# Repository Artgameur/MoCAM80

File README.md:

<p align="center">

</p>

# Table of Contents

* [Introduction](#Introduction)
* [Quick Description](#Quick-Description)
* [Firmware](#Firmware)
* [Architecture](#Architecture)
* [Features](#Features)
* [Images](#Images)
* [Components](#Components)
* [Instructions](#Instructions)
* [Schematic](#Schematic)
* [PCB](#PCB)

# Introduction

This is a project that I made for fun and to challenge myself during my second year of college as an electrical engineering student. Since I was working at 3dkeycap (a small-scale customizable keycap manufacturer), I thought about making a mechanical split keyboard. Since I was using a standard-size optical keyboard and my father is a programmer, I thought of making one for him too. This also happens to be my first GitHub repository.

Since I didn't know much about split keyboards, the thumb cluster ended up being a little unusual. Because I was making a keyboard for a programmer, it had to have a function row. At that point, I knew that the keyboard was going to be larger than standard layouts such as the Lily58 or Corne. Since it was already going to be that large, I thought, "Why not make it bigger?" So I ended up adding 80 keys.

So here is my finished project.

# Quick Description

MoCAM80 is a raspberry pi pico 2 powered 80 key split machanical keyboard. It has a reversible PCB design so that there is only one PCB version for both sides.

# Firmware

The keyboard uses custom firmware written specifically for the MoCAM80.

The left half acts as the primary controller while the right half operates as a secondary controller connected through TRRS via UART. Precompiled UF2 files are provided in the repository for both halves.

# Architecture

* Left PCB: main controller (USB HID)
* Right PCB: secondary matrix scanner
* Communication: UART via TRRS
* Firmware: custom C/C++

# Features

* A 6-key thumb cluster
* A number row
* A function row
* A 3D-printable case
* A reversible PCB (the same design is used for both sides)

# Images

# Components

## PCB Assembly

### Required
| Quantity | Component |
|----------|-----------|
| 80 | Choc V2 switches |
| 80 | MX low-profile keycaps |
| 2 | Raspberry Pi Pico 2 |
| 2 | TRRS (4-pole) female connectors |
| 1 | TRRS (4-pole) cable |
| 1 | Micro-USB data cable |

### Optional
| Quantity | Component |
|----------|-----------|
| 12 | 10 kΩ resistors (internal pull-ups are enabled) |

## Case
| Material | Quantity |
|----------|-----------|
| filament | 300g |

# Instructions

1. Once you have 2 PCBs, solder 1 Raspberry Pi Pico 2 onto each PCB.

2. Solder 1 female TRRS connector onto each PCB. (Be careful when handling them, as excessive force while plugging or unplugging the cable may lift pads from the PCB.)

3. Solder 40 switches onto one PCB and 40 switches onto the other PCB.

4. OPTIONAL: Solder 6 10 kΩ resistors onto each PCB.

5. On the left-hand PCB (the one with the switches on the same side as the Pico 2 and the TRRS connector), cut the upper two traces shown below, located near the bottom-right corner of the Pico 2.

6. On the right-hand PCB (the one with the switches on the opposite side of the Pico 2 and the TRRS connector), cut the lower two traces shown below, located near the bottom-right corner of the Pico 2.

7. Upload the [UF2 file for the main board](Software/Compiled%20Files/keyboard_Main.uf2) to the left-hand PCB.

8. Upload the [UF2 file for the secondary board](Software/Compiled%20Files/keyboard_Secondary.uf2) to the right-hand PCB.

9. Confirm that everything works correctly.

10. Print the case and assemble the final product.

# Schematic

# PCB
## Top Side

## Bottom Side

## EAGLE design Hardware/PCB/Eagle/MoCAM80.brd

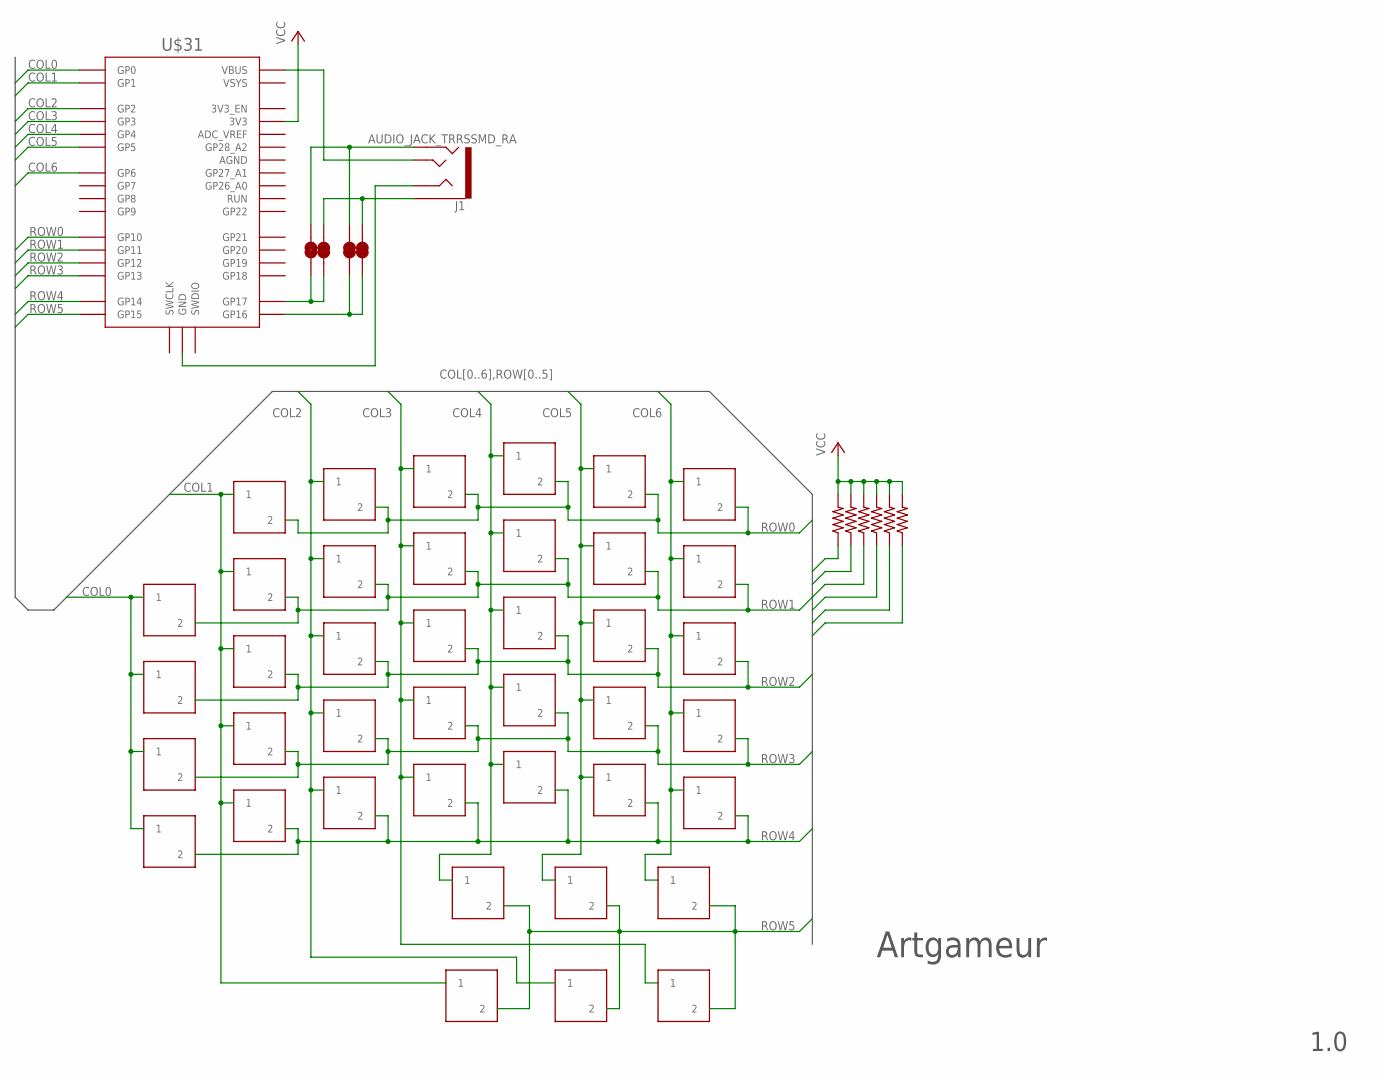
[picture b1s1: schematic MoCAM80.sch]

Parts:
J1: AUDIO_JACK_TRRSSMD_RA; AUDIO_JACK_3.5MM_TRRS_SMD_RA
JP1, JP2, JP3, JP4: JUMPER-SMT_2_NC_TRACE_NO-SILK; SMT-JUMPER_2_NC_TRACE_NO-SILK
R1, R2, R3, R4, R5, R6: R-US_CHIP-1206(3216-METRIC); RESC3216X70
U$1, U$2, U$3, U$4, U$5, U$6, U$7, U$8, U$9, U$10, U$11, U$12, U$13, U$14, U$15, U$16, U$17, U$18, U$19, U$21, U$22, U$23, U$24, U$26, U$27, U$28, U$29, U$32, U$33, U$34, U$35, U$36, U$37, U$38: KEYBOARD_SWITCHMX_CHOC_V2_SWAP; MX_CHOC_V2_SWAP
U$20, U$25: KEYBOARD_SWITCHMX_CHOC_V2_1.25; MX_CHOC_V2_1.25
U$30, U$39, U$40, U$41: KEYBOARD_SWITCHMX_CHOC_V2_1.5; MX_CHOC_V2_1.5
U$31: RPI_PICO-SMD; RPI_PICO

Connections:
COL0: U$1.P$1 (1), U$1.P$4 (1), U$2.P$1 (1), U$2.P$4 (1), U$3.P$1 (1), U$3.P$4 (1), U$31.GP0, U$38.P$1 (1), U$38.P$4 (1)
COL1: U$4.P$1 (1), U$4.P$4 (1), U$5.P$1 (1), U$5.P$4 (1), U$6.P$1 (1), U$6.P$4 (1), U$7.P$1 (1), U$7.P$4 (1), U$20.P$1 (1), U$20.P$4 (1), U$31.GP1, U$32.P$1 (1), U$32.P$4 (1)
COL2: U$8.P$1 (1), U$8.P$4 (1), U$9.P$1 (1), U$9.P$4 (1), U$10.P$1 (1), U$10.P$4 (1), U$11.P$1 (1), U$11.P$4 (1), U$25.P$1 (1), U$25.P$4 (1), U$31.GP2, U$33.P$1 (1), U$33.P$4 (1)
COL3: U$12.P$1 (1), U$12.P$4 (1), U$13.P$1 (1), U$13.P$4 (1), U$14.P$1 (1), U$14.P$4 (1), U$15.P$1 (1), U$15.P$4 (1), U$31.GP3, U$34.P$1 (1), U$34.P$4 (1), U$39.P$1 (1), U$39.P$4 (1)
COL4: U$16.P$1 (1), U$16.P$4 (1), U$17.P$1 (1), U$17.P$4 (1), U$18.P$1 (1), U$18.P$4 (1), U$19.P$1 (1), U$19.P$4 (1), U$30.P$1 (1), U$30.P$4 (1), U$31.GP4, U$35.P$1 (1), U$35.P$4 (1)
COL5: U$21.P$1 (1), U$21.P$4 (1), U$22.P$1 (1), U$22.P$4 (1), U$23.P$1 (1), U$23.P$4 (1), U$24.P$1 (1), U$24.P$4 (1), U$31.GP5, U$36.P$1 (1), U$36.P$4 (1), U$40.P$1 (1), U$40.P$4 (1)
COL6: U$26.P$1 (1), U$26.P$4 (1), U$27.P$1 (1), U$27.P$4 (1), U$28.P$1 (1), U$28.P$4 (1), U$29.P$1 (1), U$29.P$4 (1), U$31.GP6, U$37.P$1 (1), U$37.P$4 (1), U$41.P$1 (1), U$41.P$4 (1)
JACK_1: J1.TIP, U$31.VBUS
JACK_2: J1.RING2, JP2.2, JP4.2
JACK_GND: J1.RING1, U$31.GND@1 (GND), U$31.GND@2 (GND), U$31.GND@3 (GND), U$31.GND@4 (GND), U$31.GND@5 (GND), U$31.GND@6 (GND), U$31.GND@7 (GND), U$31.GND@8 (GND)
JACK_TIP: J1.EARTH, JP1.2, JP3.2
ROW0: R6.1, U$31.GP10, U$32.P$2 (2), U$33.P$2 (2), U$34.P$2 (2), U$35.P$2 (2), U$36.P$2 (2), U$37.P$2 (2)
ROW1: R1.1, U$4.P$2 (2), U$8.P$2 (2), U$12.P$2 (2), U$16.P$2 (2), U$21.P$2 (2), U$26.P$2 (2), U$31.GP11, U$38.P$2 (2)
ROW2: R2.1, U$1.P$2 (2), U$5.P$2 (2), U$9.P$2 (2), U$13.P$2 (2), U$17.P$2 (2), U$22.P$2 (2), U$27.P$2 (2), U$31.GP12
ROW3: R3.1, U$2.P$2 (2), U$6.P$2 (2), U$10.P$2 (2), U$14.P$2 (2), U$18.P$2 (2), U$23.P$2 (2), U$28.P$2 (2), U$31.GP13
ROW4: R4.1, U$3.P$2 (2), U$7.P$2 (2), U$11.P$2 (2), U$15.P$2 (2), U$19.P$2 (2), U$24.P$2 (2), U$29.P$2 (2), U$31.GP14
ROW5: R5.1, U$20.P$2 (2), U$25.P$2 (2), U$30.P$2 (2), U$31.GP15, U$39.P$2 (2), U$40.P$2 (2), U$41.P$2 (2)
UART_RX: JP1.1, JP4.1, U$31.GP17
UART_TX: JP2.1, JP3.1, U$31.GP16
VCC: R1.2, R2.2, R3.2, R4.2, R5.2, R6.2, U$31.3V3

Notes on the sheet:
Artgameur
1.0

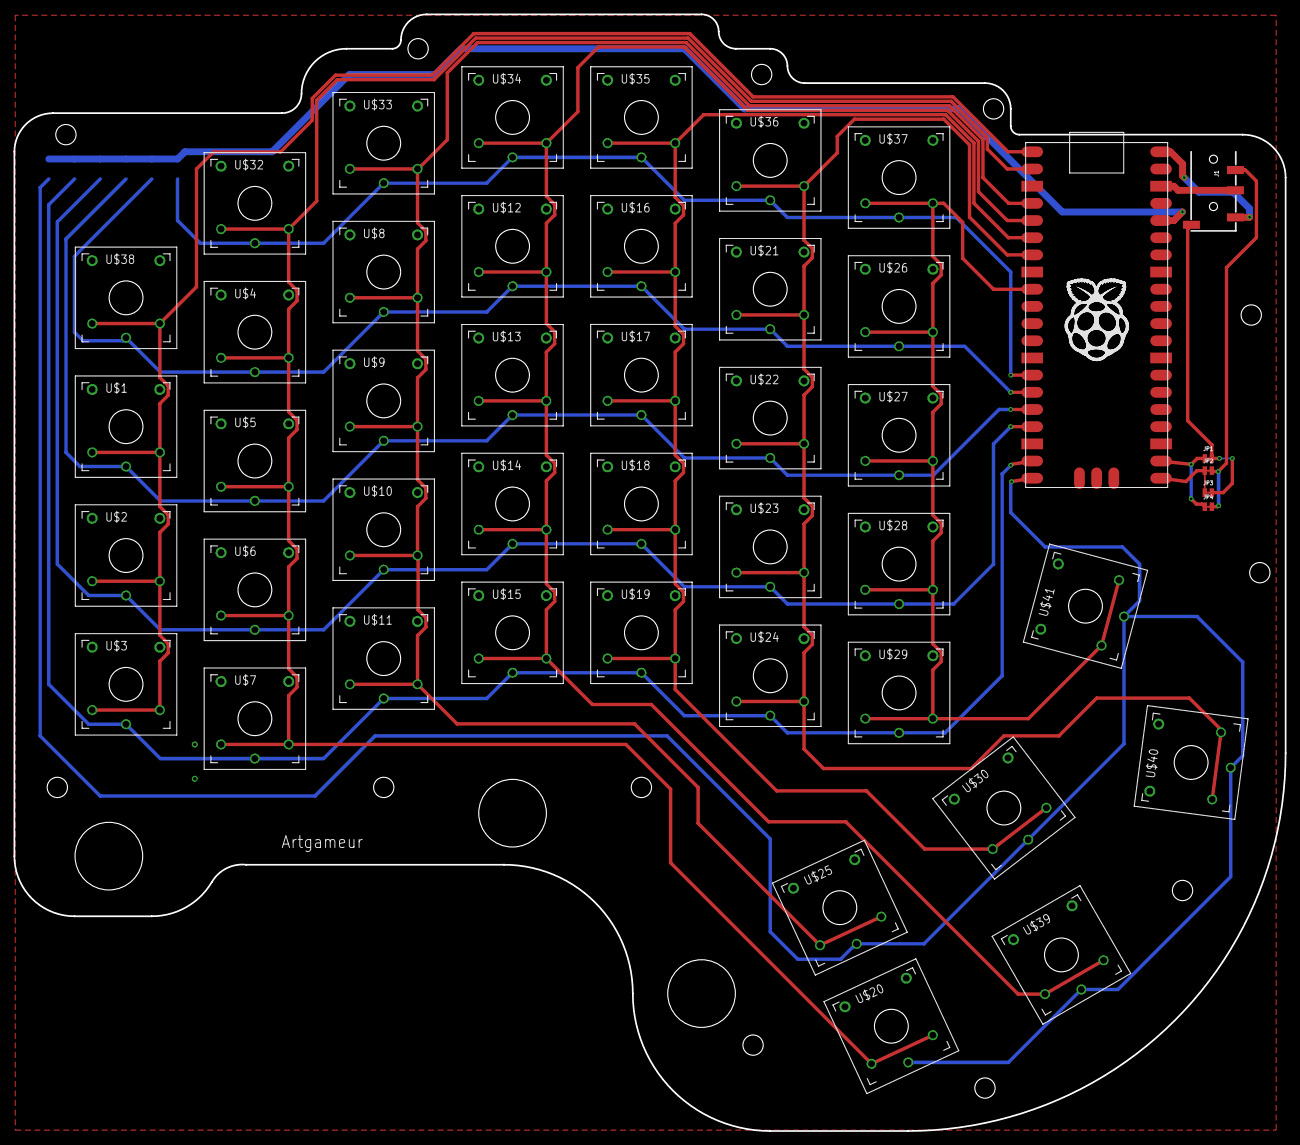
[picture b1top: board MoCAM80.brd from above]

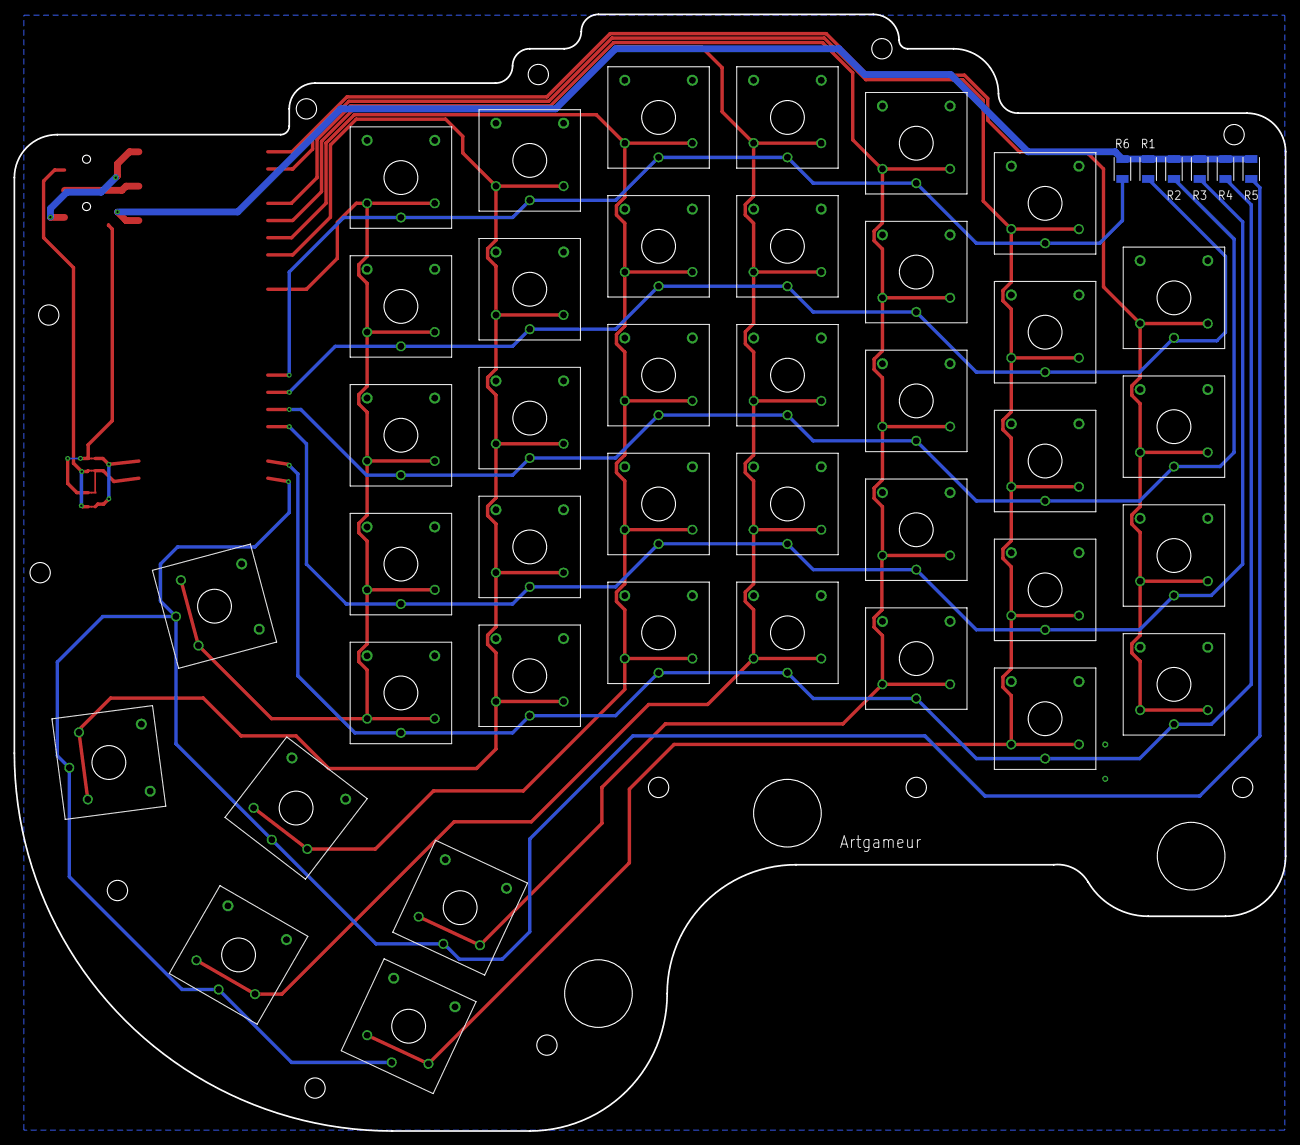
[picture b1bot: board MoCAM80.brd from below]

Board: 2 copper layers, 188.0 x 165.1 mm, 52 parts (6 on the bottom side), 20 nets.

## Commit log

2026-06-13 Create README.md with project overview and features
    Added a README file with project details, features, and images.
2026-06-13 Add CERN Open Hardware Licence Version 2
2026-06-13 Add CERN License file
2026-06-13 Add GNU General Public License version 3
2026-06-13 Rename License-CERN to LICENSE-CERN
2026-06-13 Update README with Components and Instructions
    Added sections for Components and Instructions to the README.
2026-06-13 Fix formatting in assembly instructions
    Removed an empty line in the assembly instructions.
2026-06-13 Revise README for clarity and structure
    Updated the README to improve clarity and structure, including corrections to spelling and grammar. Added a firmware section and formatted the components and instructions tables.
2026-06-13 Add Schematic and PCB sections to README
    Added sections for Schematic and PCB with images.
2026-06-13 Add image to README and update table of contents
2026-06-13 Fix typo in README.md for 'Quantity' header
2026-06-13 Enhance README with Architecture section and terminology update
    Added Architecture section to README and updated terminology.
2026-06-13 Add Quick Description section to README
    Added a quick description section for MoCAM80 keyboard.
2026-06-13 Update Quick Description link in README
2026-06-13 Fix Table of Contents links and header formatting
    Updated links in the Table of Contents and corrected header formatting.
2026-06-13 Update PCB images in README
    Replaced images for the top and bottom sides of the PCB.
2026-06-13 Fix typo in README.md for 'Quantity'
2026-06-14 Rename README.md to README.en.md
2026-06-14 Rename README.en.md to README.md
2026-06-14 Add French README translation for MoCAM80 project
    Added French translation of the README file, including project details, specifications, and assembly instructions for the MoCAM80 mechanical keyboard.
2026-06-14 Add language badges and update README structure
2026-06-14 Add language flags to README badges
2026-06-21 Add new images to README.md
2026-06-21 Add additional images to README.fr.md
